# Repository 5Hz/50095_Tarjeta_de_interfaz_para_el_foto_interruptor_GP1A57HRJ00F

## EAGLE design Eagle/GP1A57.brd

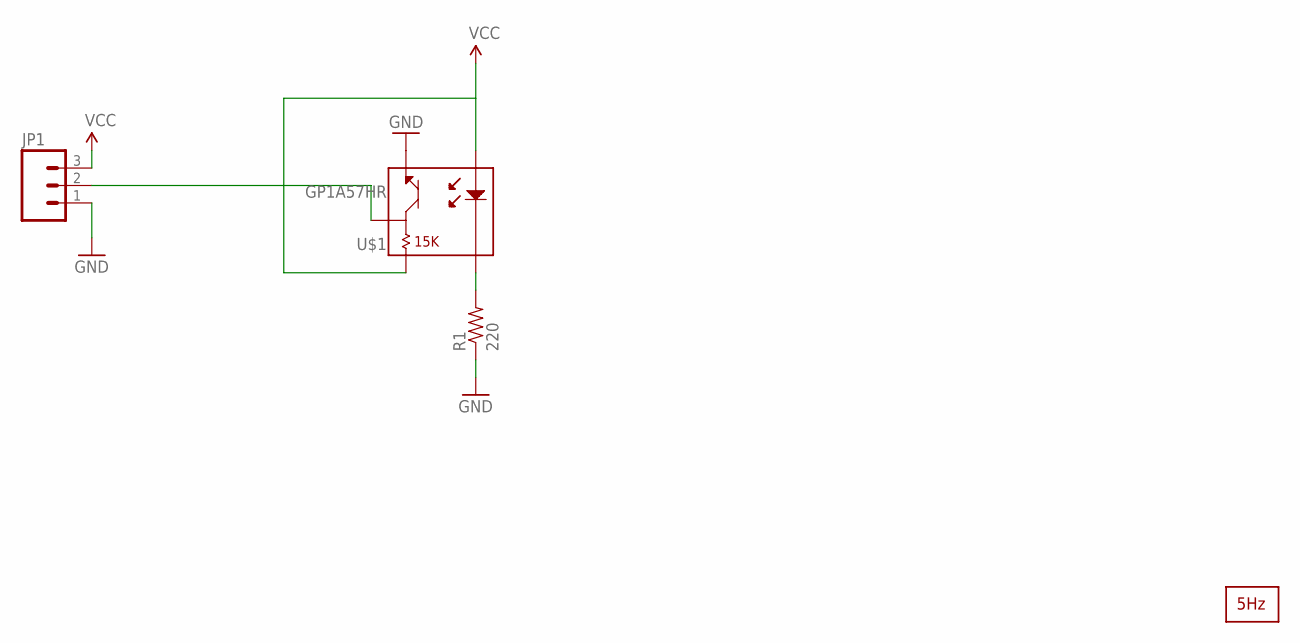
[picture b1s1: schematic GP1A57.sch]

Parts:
JP1: M03PTH; 1X03
R1: 220; AXIAL-0.4
U$1: GP1A57HR
U$2: LOGO2_SILKL10MM; LARGO2_10MM

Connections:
GND: JP1.1, R1.P$1 (1), U$1.5
unnamed: R1.P$2 (2), U$1.2
unnamed: JP1.2, U$1.4
VCC: JP1.3, U$1.1, U$1.3

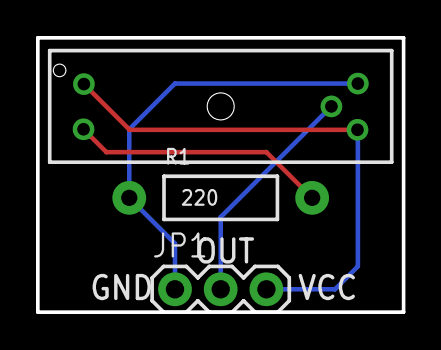
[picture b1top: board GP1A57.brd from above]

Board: 2 copper layers, 20.3 x 15.2 mm, 4 parts (1 on the bottom side), 4 nets.

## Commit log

2014-01-13 creación

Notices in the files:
parts and their libraries:
SparkFun: Licensing: CC v3.0 Share-Alike You are welcome to use this library for commercial purposes.
